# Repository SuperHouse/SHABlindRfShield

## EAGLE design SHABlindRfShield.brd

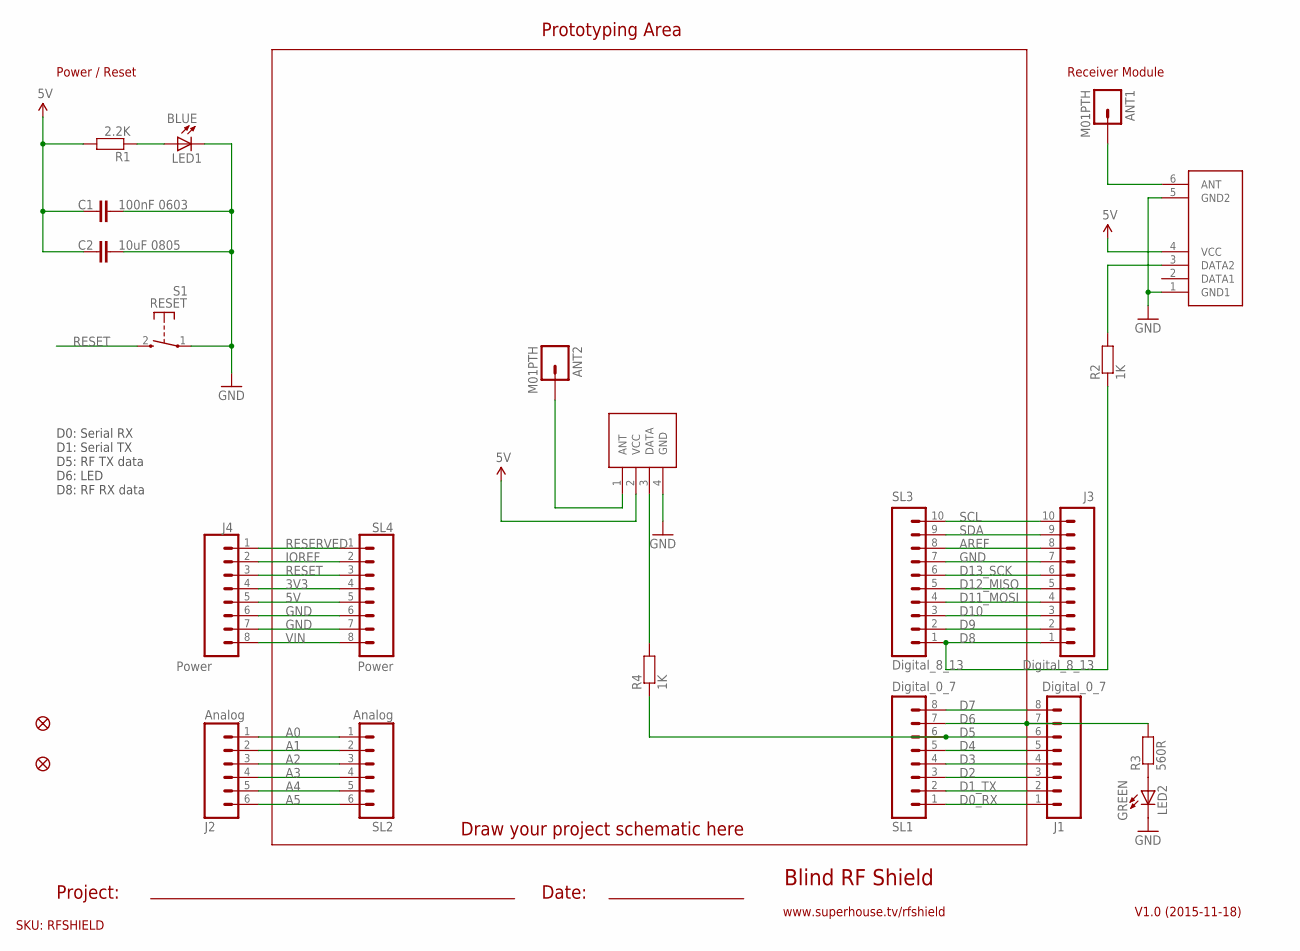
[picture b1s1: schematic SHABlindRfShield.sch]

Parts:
ANT1, ANT2: M01PTH; 1X01
C1: 100nF 0603; 0603
C2: 10uF 0805; C0805
IC3: RXB1; RX-B1-SHORT-FLAT
IC4: TX-C1FLAT; TX-C1-FLAT
J1: Digital_0_7; 1X08
J2: Analog; 1X06
J3: Digital_8_13; 1X10
J4: Power; 1X08
LED1: BLUE; LED-0603
LED2: GREEN; LED-0603
R1: 2.2K; 0603
R2, R4: 1K; 0603
R3: 560R; 0603
S1: RESET; TACTILE_SWITCH_SMD_2PIN_TINY
SL1: Digital_0_7; 1X08
SL2: Analog; 1X06
SL3: Digital_8_13; 1X10
SL4: Power; 1X08
U$4, U$5: FIDUCIAL1X2.5; FIDUCIAL-1X2.5

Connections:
3V3: J4.4, SL4.4
5V: C1.1, C2.2, IC3.4 (VCC), IC4.2 (VCC), J4.5, R1.2, SL4.5
A0: J2.1, SL2.1
A1: J2.2, SL2.2
A2: J2.3, SL2.3
A3: J2.4, SL2.4
A4: J2.5, SL2.5
A5: J2.6, SL2.6
AREF: J3.8, SL3.8
D0_RX: J1.1, SL1.1
D1_TX: J1.2, SL1.2
D2: J1.3, SL1.3
D3: J1.4, SL1.4
D4: J1.5, SL1.5
D5: J1.6, R4.1, SL1.6
D6: J1.7, R3.2, SL1.7
D7: J1.8, SL1.8
D8: J3.1, R2.1, SL3.1
D9: J3.2, SL3.2
D10: J3.3, SL3.3
D11_MOSI: J3.4, SL3.4
D12_MISO: J3.5, SL3.5
D13_SCK: J3.6, SL3.6
GND: C1.2, C2.1, IC3.1 (GND1), IC3.5 (GND2), IC4.4 (GND), J3.7, J4.6, J4.7, LED1.C, LED2.C, S1.1, SL3.7, SL4.6, SL4.7
IOREF: J4.2, SL4.2
unnamed: LED1.A, R1.1
unnamed: LED2.A, R3.1
unnamed: ANT1.1, IC3.6 (ANT)
unnamed: ANT2.1, IC4.1 (ANT)
unnamed: IC4.3 (DATA), R4.2
unnamed: IC3.3 (DATA2), R2.2
RESERVED: J4.1, SL4.1
RESET: J4.3, S1.2 (S), SL4.3
SCL: J3.10, SL3.10
SDA: J3.9, SL3.9
VIN: J4.8, SL4.8

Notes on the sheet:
Prototyping Area
Blind RF Shield
SKU: RFSHIELD
V1.0 (2015-11-18)
Power / Reset
Draw your project schematic here
Project:
Date:
Receiver Module
www.superhouse.tv/rfshield
D0: Serial RX D1: Serial TX D5: RF TX data D6: LED D8: RF RX data

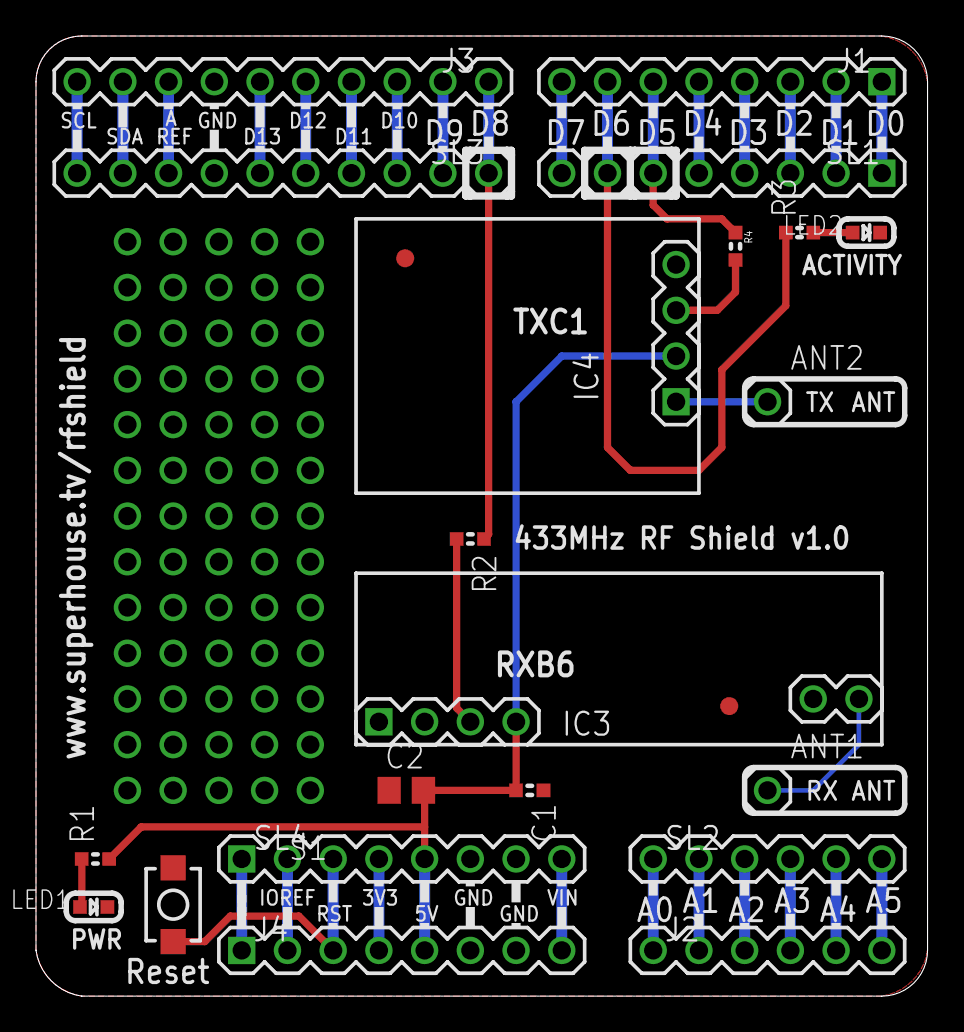
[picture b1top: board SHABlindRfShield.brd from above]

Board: 2 copper layers, 49.5 x 53.3 mm, 23 parts (0 on the bottom side), 36 nets.

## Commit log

2015-11-18 Initial import from receiver shield project
2019-04-24 Routing and silkscreen

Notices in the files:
SHABlindRfShield.brd:
(C)2015 SuperHouse Automation P/L
